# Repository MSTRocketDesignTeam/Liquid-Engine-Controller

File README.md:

<p align="center"><sup><em>*This repo is intended for educational purposes only*</em></sup></p>

# SRAD Engine Controller
A student researched and designed (SRAD) engine controller for the liquid bipropellant rocket. 

## About
This project is the first iteration of the flight controller for the Rocket Design Team's (RDT) liquid bipropellant rocket.
It aims to provide basic engine control functionality, such as opening and closing of the servo ball valves (SBV), as well as to set the hardware baseline for more advanced control functionality like throttling algorithms for flight efficiency. Additionally, the Liquid Engine Controller (LEC) aims to serve as the data acquisition computer for the propulsion system, in order to analyze the performance of the propulsion system. 

## Documentation
*placeholder*

## Development 
*placeholder* 

## File Structure
This repo contains three main sections, hardware, firmware, and software.

### Hardware:
The hardware directory will contain all of the files related to the design and assembly of the PCBs. This includes KiCad projects as well as BOMs. 

### Firmware:
The firmware directory will contain all of the code (C++) necessary to operate the above hardware. Once the boards have been designed and assembled this is where significant effort will be made.

### Software: 
The software directory will contain the code (Python) for the LEC's computer interface. This program will be responsible for configuring the LEC prior to launch as well as for displaying live propulsion system state data from the launch pad. 

Future developments may allow for preflight simulations (FEA / CFD of engine, estimated throttling curve, etc.).

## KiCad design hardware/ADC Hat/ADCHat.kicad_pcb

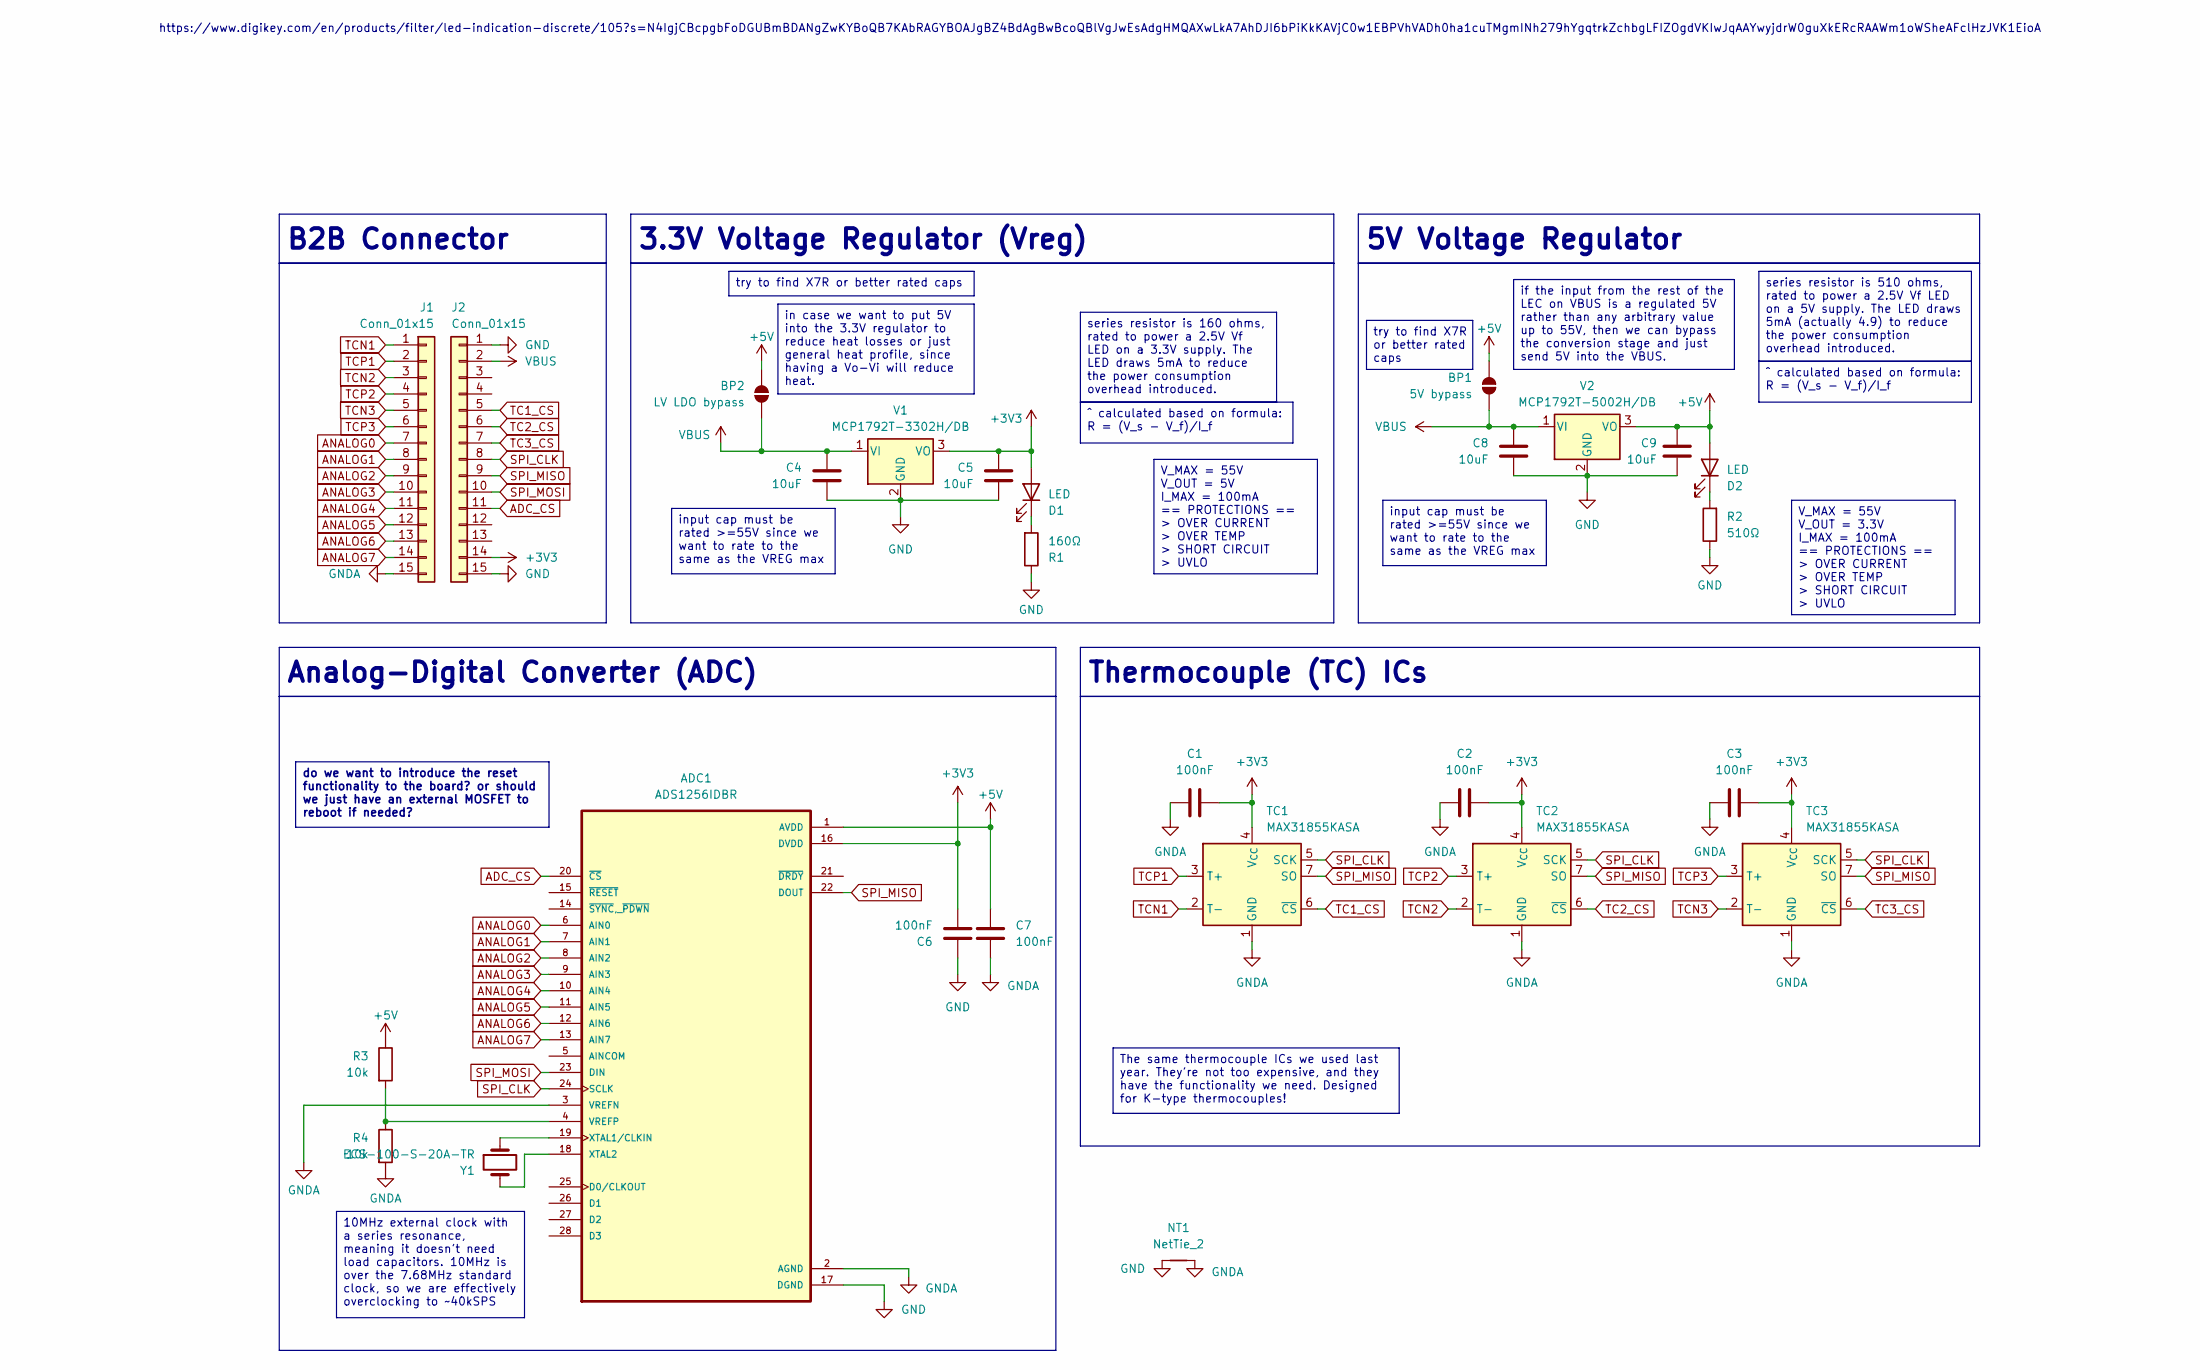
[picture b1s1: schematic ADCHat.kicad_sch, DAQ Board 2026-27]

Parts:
ADC1: ADS1256IDBR; SOP65P780X200-28N; DIGIKEY_ID ADS1256IDBR
BP1: 5V bypass; SolderJumper-2_P1.3mm_Open_RoundedPad1.0x1.5mm
BP2: LV LDO bypass; SolderJumper-2_P1.3mm_Open_RoundedPad1.0x1.5mm
C1, C2, C3: 100nF; C_0402_1005Metric; DIGIKEY_ID GRM155R71H104KE14D
C4, C8: 10uF; C_0805_2012Metric; DIGIKEY_ID GMC21X5R106K50NT
C5, C9: 10uF; C_0805_2012Metric; DIGIKEY_ID CL21A106KPFNNNG
C6, C7: 100nF; C_0805_2012Metric; DIGIKEY_ID CL21B104KBCNNNC
D1, D2: LED; LED_0603_1608Metric; DIGIKEY_ID KT EELP41.12-S2U1-25-2X4Y-5-R18
J1, J2: Conn_01x15; PinHeader_1x15_P2.54mm_Vertical
NT1: NetTie_2; NetTie-2_SMD_Pad0.5mm
R1: 160Ω; R_0603_1608Metric; DIGIKEY_ID RC0402FR-07160RL
R2: 510Ω; R_0603_1608Metric; DIGIKEY_ID RC0402FR-07510RL
R3, R4: 10k; R_0603_1608Metric; DIGIKEY_ID RNCF0402BTE10K0
TC1, TC2, TC3: MAX31855KASA; SOIC-8_3.9x4.9mm_P1.27mm; DIGIKEY_ID MAX31855KASA+T
V1: MCP1792T-3302H/DB; SOT-223-3_TabPin2; DIGIKEY_ID MCP1792T-3302H/DB
V2: MCP1792T-5002H/DB; SOT-223-3_TabPin2; DIGIKEY_ID MCP1792T-5002H/DB
Y1: ECS-100-S-20A-TR; XTAL_ECS-100-S-20A-TR; DIGIKEY_ID ECS-100-S-20A-TR

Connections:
+3V3: ADC1.16 (DVDD), C1.2, C2.2, C3.2, C5.1, C6.1, D1.2 (A), J2.14, TC1.4 (V_{CC}), TC2.4 (V_{CC}), TC3.4 (V_{CC}), V1.3 (VO)
+5V: ADC1.1 (AVDD), BP1.2 (B), BP2.2 (B), C7.2, C9.1, D2.2 (A), R3.1, V2.3 (VO)
ADC_CS: ADC1.20 (~CS), J2.11
ANALOG0: ADC1.6 (AIN0), J1.7
ANALOG1: ADC1.7 (AIN1), J1.8
ANALOG2: ADC1.8 (AIN2), J1.9
ANALOG3: ADC1.9 (AIN3), J1.10
ANALOG4: ADC1.10 (AIN4), J1.11
ANALOG5: ADC1.11 (AIN5), J1.12
ANALOG6: ADC1.12 (AIN6), J1.13
ANALOG7: ADC1.13 (AIN7), J1.14
GND: ADC1.17 (DGND), C4.2, C5.2, C6.2, C8.2, C9.2, J2.1, J2.15, NT1.1, R1.1, R2.1, V1.2 (GND), V2.2 (GND)
GNDA: ADC1.2 (AGND), ADC1.3 (VREFN), C1.1, C2.1, C3.1, C7.1, J1.15, NT1.2, R4.2, TC1.1 (GND), TC2.1 (GND), TC3.1 (GND)
unnamed: ADC1.4 (VREFP), R3.2, R4.1
unnamed: ADC1.19 (XTAL1/CLKIN), Y1.1
unnamed: ADC1.18 (XTAL2), Y1.2
unnamed: D1.1 (K), R1.2
unnamed: D2.1 (K), R2.2
SPI_CLK: ADC1.24 (SCLK), J2.8, TC1.5 (SCK), TC2.5 (SCK), TC3.5 (SCK)
SPI_MISO: ADC1.22 (DOUT), J2.9, TC1.7 (SO), TC2.7 (SO), TC3.7 (SO)
SPI_MOSI: ADC1.23 (DIN), J2.10
TC1_CS: J2.5, TC1.6 (~CS)
TC2_CS: J2.6, TC2.6 (~CS)
TC3_CS: J2.7, TC3.6 (~CS)
TCN1: J1.1, TC1.2 (T-)
TCN2: J1.3, TC2.2 (T-)
TCN3: J1.5, TC3.2 (T-)
TCP1: J1.2, TC1.3 (T+)
TCP2: J1.4, TC2.3 (T+)
TCP3: J1.6, TC3.3 (T+)
VBUS: BP1.1 (A), BP2.1 (A), C4.1, C8.1, J2.2, V1.1 (VI), V2.1 (VI)

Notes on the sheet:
https://www.digikey.com/en/products/filter/led-indication-discrete/105?s=N4IgjCBcpgbFoDGUBmBDANgZwKYBoQB7KAbRAGYBOAJgBZ4BdAgBwBcoQBlVgJwEsAdgHMQAXwLkA7AhDJI6bPiKkKAVjC0w1EBPVhVADh0ha1cuTMgmINh279hYgqtrkZchbgLFIZOgdVKIwJqAAYwyjdrW0guXkERcRAAWm1oWSheAFclHzJVK1EioA
10MHz external clock with a series resonance, meaning it doesn't need load capacitors. 10MHz is over the 7.68MHz standard clock, so we are effectively overclocking to ~40kSPS
in case we want to put 5V into the 3.3V regulator to reduce heat losses or just general heat profile, since having a Vo-Vi will reduce heat.
input cap must be rated >=55V since we want to rate to the same as the VREG max
5V Voltage Regulator
try to find X7R or better rated caps
V_MAX = 55V V_OUT = 5V I_MAX = 100mA == PROTECTIONS == > OVER CURRENT > OVER TEMP > SHORT CIRCUIT > UVLO
^ calculated based on formula: R = (V_s - V_f)/I_f
do we want to introduce the reset functionality to the board? or should we just have an external MOSFET to reboot if needed?
if the input from the rest of the LEC on VBUS is a regulated 5V rather than any arbitrary value up to 55V, then we can bypass the conversion stage and just send 5V into the VBUS.
Analog-Digital Converter (ADC)
The same thermocouple ICs we used last year. They're not too expensive, and they have the functionality we need. Designed for K-type thermocouples!
3.3V Voltage Regulator (Vreg)
V_MAX = 55V V_OUT = 3.3V I_MAX = 100mA == PROTECTIONS == > OVER CURRENT > OVER TEMP > SHORT CIRCUIT > UVLO
series resistor is 160 ohms, rated to power a 2.5V Vf LED on a 3.3V supply. The LED draws 5mA to reduce the power consumption overhead introduced.
series resistor is 510 ohms, rated to power a 2.5V Vf LED on a 5V supply. The LED draws 5mA (actually 4.9) to reduce the power consumption overhead introduced.
Thermocouple (TC) ICs
B2B Connector

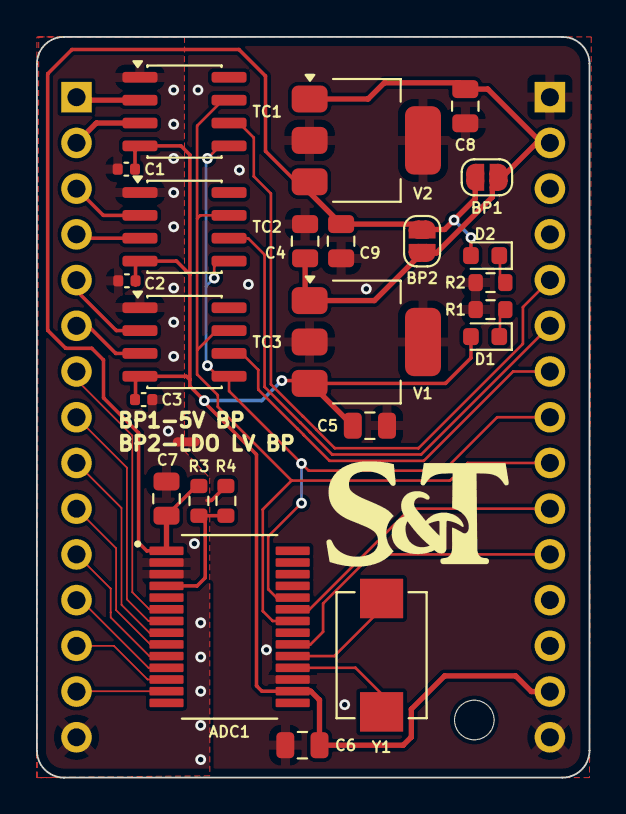
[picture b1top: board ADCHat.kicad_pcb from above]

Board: 2 copper layers, 30.7 x 41.1 mm, 27 parts (0 on the bottom side), 31 nets.

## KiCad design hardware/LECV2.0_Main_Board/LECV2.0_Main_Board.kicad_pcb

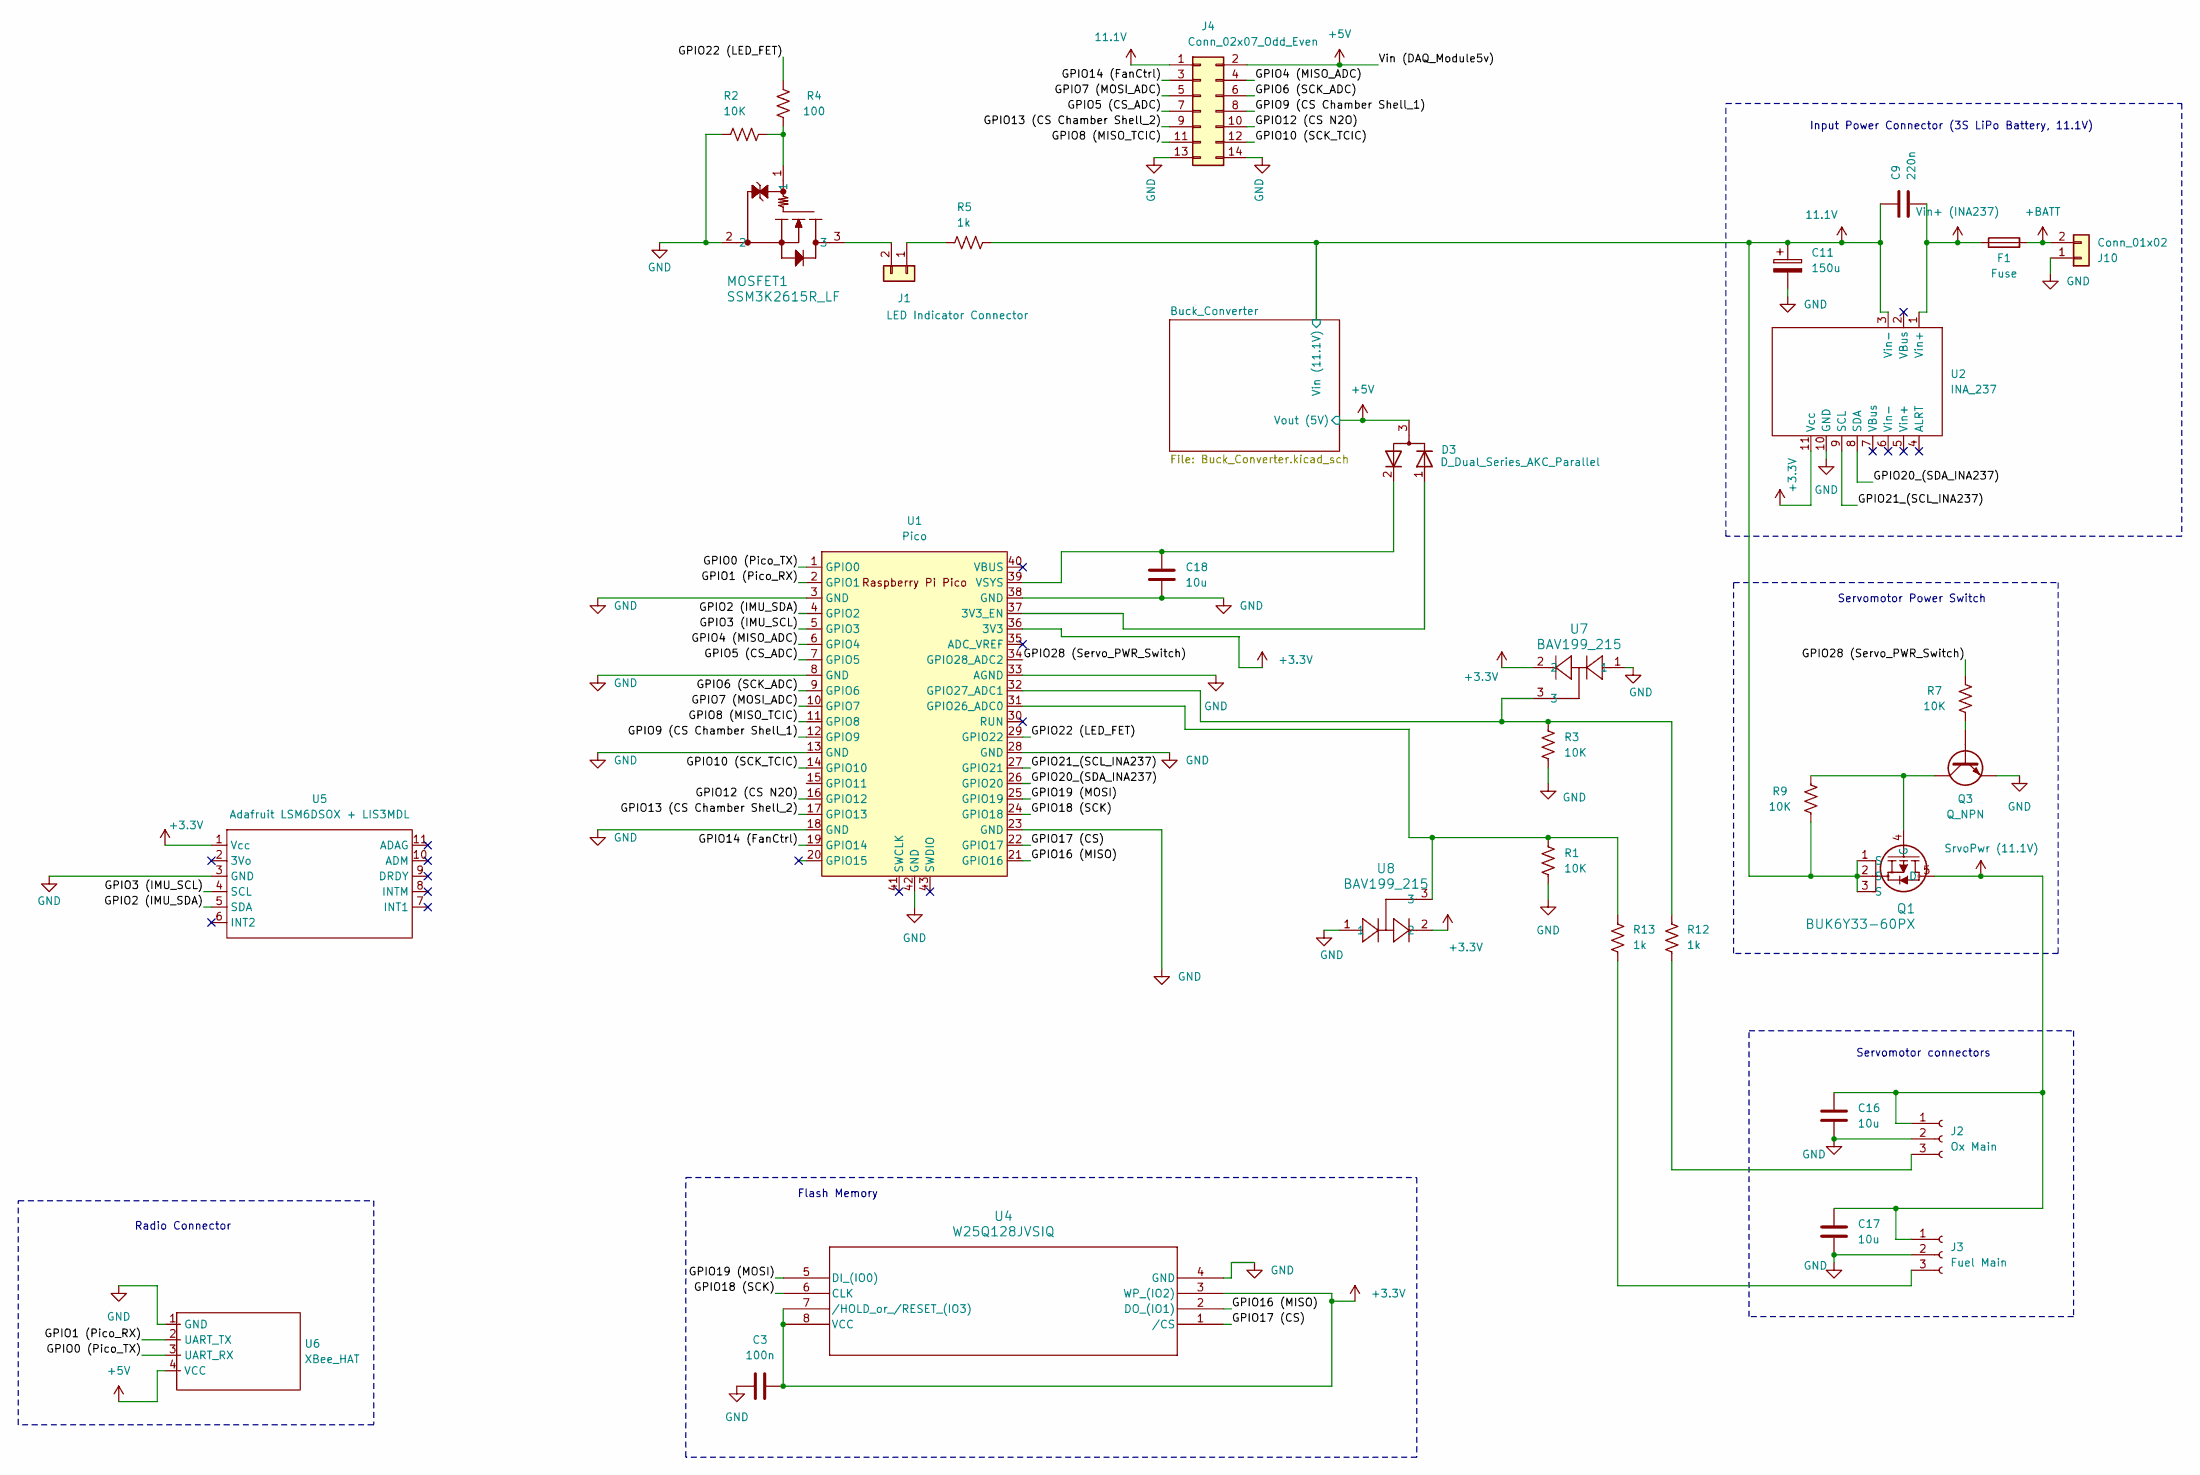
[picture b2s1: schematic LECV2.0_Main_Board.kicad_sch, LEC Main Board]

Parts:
C3: 100n; C_0603_1608Metric
C9: 220n; C_0805_2012Metric
C11: 150u; CAPPRD500W60D1000H1600
C16, C17, C18: 10u; C_1210_3225Metric
D3: D_Dual_Series_AKC_Parallel; SOT-23
F1: Fuse; Fuse_1206_3216Metric
J1: LED Indicator Connector; PinHeader_1x02_P2.54mm_Vertical
J2: Ox Main; TENSILITY_54-00440
J3: Fuel Main; TENSILITY_54-00440
J4: Conn_02x07_Odd_Even; PinHeader_2x07_P2.54mm_Vertical
J10: Conn_01x02; AMASS_XT30UPB-M_1x02_P5.0mm_Vertical
MOSFET1: SSM3K2615R_LF; SOT-23F_TOS
Q1: BUK6Y33-60PX; LFPAK_SOT669_NEX
Q3: Q_NPN; SOT-323_SC-70
R1, R2, R3, R7, R9: 10K; R_0603_1608Metric
R4: 100; R_0603_1608Metric
R5, R12, R13: 1k; R_0603_1608Metric
U1: Pico; RPi_Pico_SMD_TH
U2: INA_237; INA238_MODULE
U4: W25Q128JVSIQ; SOIC_128JVSIQ_WIN
U5: Adafruit LSM6DSOX + LIS3MDL; Adafruit_LSM6DSOX+LIS3MDL
U6: XBee_HAT; XBee-HAT
U7, U8: BAV199_215; SOT-23-3

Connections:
11.1V: C9.1, C11.1, J4.1, Q1.1 (S), Q1.2 (S), Q1.3 (S), R5.2, R9.1, U2.3 (Vin-); also elsewhere on the board
+3.3V: C3.2, U1.36 (3V3), U2.11 (Vcc), U4.3 (WP_(IO2)), U4.7 (/HOLD_or_/RESET_(IO3)), U4.8 (VCC), U5.1 (Vcc), U7.2, U8.2
+5V: D3.3 (common), J4.2, U6.4 (VCC); also elsewhere on the board
+BATT: F1.2, J10.2
/GPIO0 (Pico_TX): U1.1 (GPIO0), U6.3 (UART_RX)
/GPIO1 (Pico_RX): U1.2 (GPIO1), U6.2 (UART_TX)
/GPIO2 (IMU_SDA): U1.4 (GPIO2), U5.5 (SDA)
/GPIO3 (IMU_SCL): U1.5 (GPIO3), U5.4 (SCL)
/GPIO4 (MISO_ADC): J4.4, U1.6 (GPIO4)
/GPIO5 (CS_ADC): J4.7, U1.7 (GPIO5)
/GPIO6 (SCK_ADC): J4.6, U1.9 (GPIO6)
/GPIO7 (MOSI_ADC): J4.5, U1.10 (GPIO7)
/GPIO8 (MISO_TCIC): J4.11, U1.11 (GPIO8)
/GPIO9 (CS Chamber Shell_1): J4.8, U1.12 (GPIO9)
/GPIO10 (SCK_TCIC): J4.12, U1.14 (GPIO10)
/GPIO12 (CS N2O): J4.10, U1.16 (GPIO12)
/GPIO13 (CS Chamber Shell_2): J4.9, U1.17 (GPIO13)
/GPIO14 (FanCtrl): J4.3, U1.19 (GPIO14)
/GPIO16 (MISO): U1.21 (GPIO16), U4.2 (DO_(IO1))
/GPIO17 (CS): U1.22 (GPIO17), U4.1 (/CS)
/GPIO18 (SCK): U1.24 (GPIO18), U4.6 (CLK)
/GPIO19 (MOSI): U1.25 (GPIO19), U4.5 (DI_(IO0))
/GPIO20_(SDA_INA237): U1.26 (GPIO20), U2.8 (SDA)
/GPIO21_(SCL_INA237): U1.27 (GPIO21), U2.9 (SCL)
/GPIO22 (LED_FET): R4.1, U1.29 (GPIO22)
/GPIO28 (Servo_PWR_Switch): R7.2, U1.34 (GPIO28_ADC2)
GND: C3.1, C11.2, C16.2, C17.2, C18.2, J2.2, J3.2, J4.13, J4.14, J10.1, MOSFET1.2, Q3.2 (E), R1.2, R2.2, R3.2, U1.3 (GND), U1.8 (GND), U1.13 (GND), U1.18 (GND), U1.23 (GND), U1.28 (GND), U1.33 (AGND), U1.38 (GND), U1.42 (GND), U2.10 (GND), U4.4 (GND), U5.3 (GND), U6.1 (GND), U7.1, U8.1; also elsewhere on the board
unnamed: D3.1 (A), U1.37 (3V3_EN)
unnamed: C18.1, D3.2 (K), U1.39 (VSYS)
unnamed: J1.1, R5.1
unnamed: J1.2, MOSFET1.3
unnamed: J2.3, R12.2
unnamed: J3.3, R13.2
unnamed: MOSFET1.1, R2.1, R4.2
unnamed: Q1.4 (G), Q3.3 (C), R9.2
unnamed: Q3.1 (B), R7.1
unnamed: R1.1, R13.1, U1.31 (GPIO26_ADC0), U8.3
unnamed: R3.1, R12.1, U1.32 (GPIO27_ADC1), U7.3
SrvoPwr (11.1V): C16.1, C17.1, J2.1, J3.1, Q1.5 (D)
Vin+ (INA237): C9.2, F1.1, U2.1 (Vin+)

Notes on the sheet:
Flash Memory
Radio Connector
Servomotor Power Switch
Input Power Connector (3S LiPo Battery, 11.1V)
Servomotor connectors

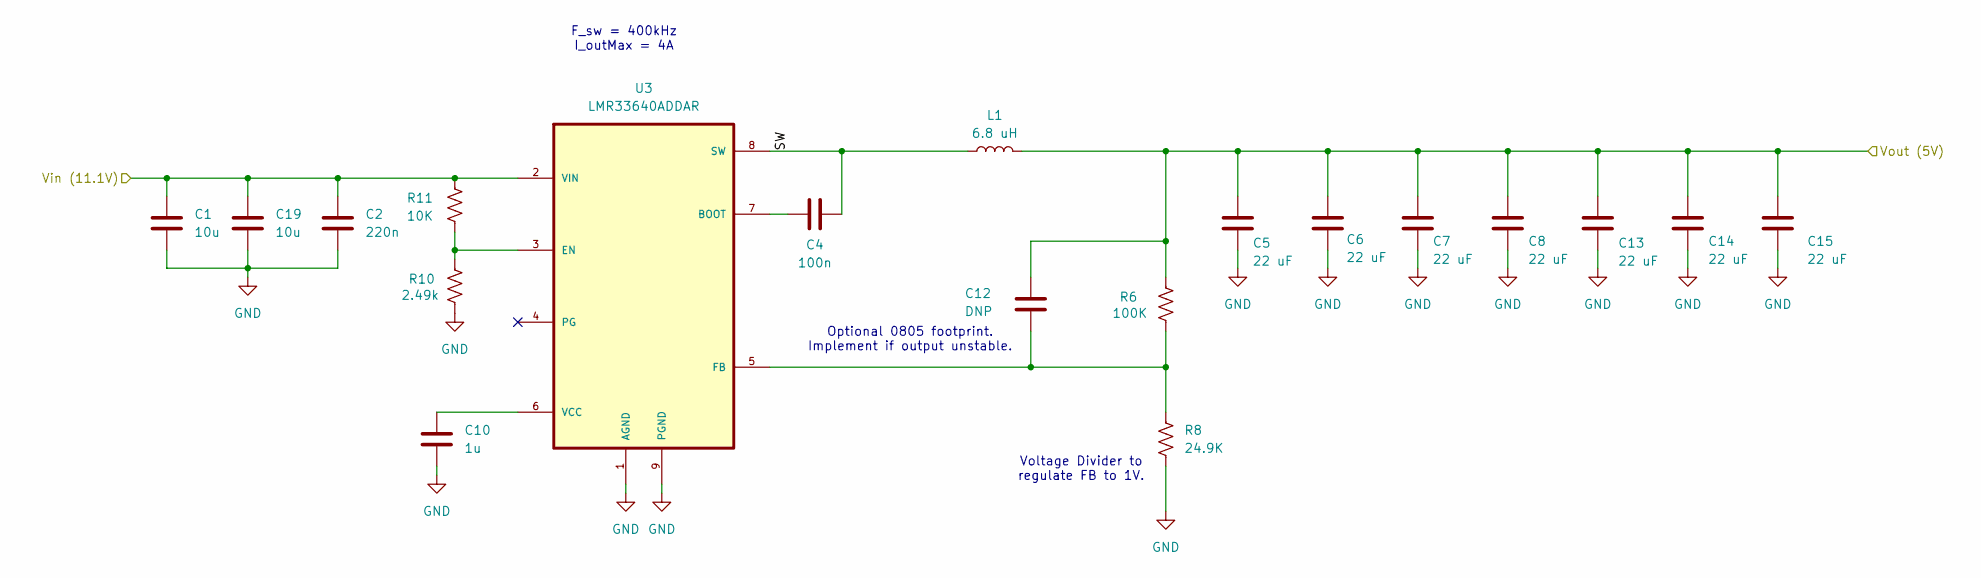
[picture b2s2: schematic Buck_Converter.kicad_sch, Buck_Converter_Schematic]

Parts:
C1, C19: 10u; C_1210_3225Metric
C2: 220n; C_0805_2012Metric
C4: 100n; C_0603_1608Metric
C5, C6, C7, C8, C13, C14, C15: 22 uF; C_0805_2012Metric
C10: 1u; C_0805_2012Metric
C12: DNP; C_0805_2012Metric
L1: 6.8 uH; IND_CSBX0650-6R8M
R6: 100K; R_0603_1608Metric
R8: 24.9K; R_0603_1608Metric
R10: 2.49k; R_0603_1608Metric
R11: 10K; R_0603_1608Metric
U3: LMR33640ADDAR; Texas_HSOP-8-1EP_3.9x4.9mm_P1.27mm_ThermalVias

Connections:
11.1V: C1.1, C2.1, C19.1, R11.1, U3.2 (VIN); also elsewhere on the board
+5V: C5.1, C6.1, C7.1, C8.1, C12.2, C13.1, C14.1, C15.1, L1.2, R6.2; also elsewhere on the board
/Buck_Converter/SW: C4.2, L1.1, U3.8 (SW)
GND: C1.2, C2.2, C5.2, C6.2, C7.2, C8.2, C10.2, C13.2, C14.2, C15.2, C19.2, R8.2, R10.1, U3.1 (AGND), U3.9 (PGND); also elsewhere on the board
unnamed: C4.1, U3.7 (BOOT)
unnamed: R10.2, R11.2, U3.3 (EN)
unnamed: C12.1, R6.1, R8.1, U3.5 (FB)
unnamed: C10.1, U3.6 (VCC)

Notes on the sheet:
Optional 0805 footprint. Implement if output unstable.
Voltage Divider to regulate FB to 1V.
F_sw = 400kHz I_outMax = 4A

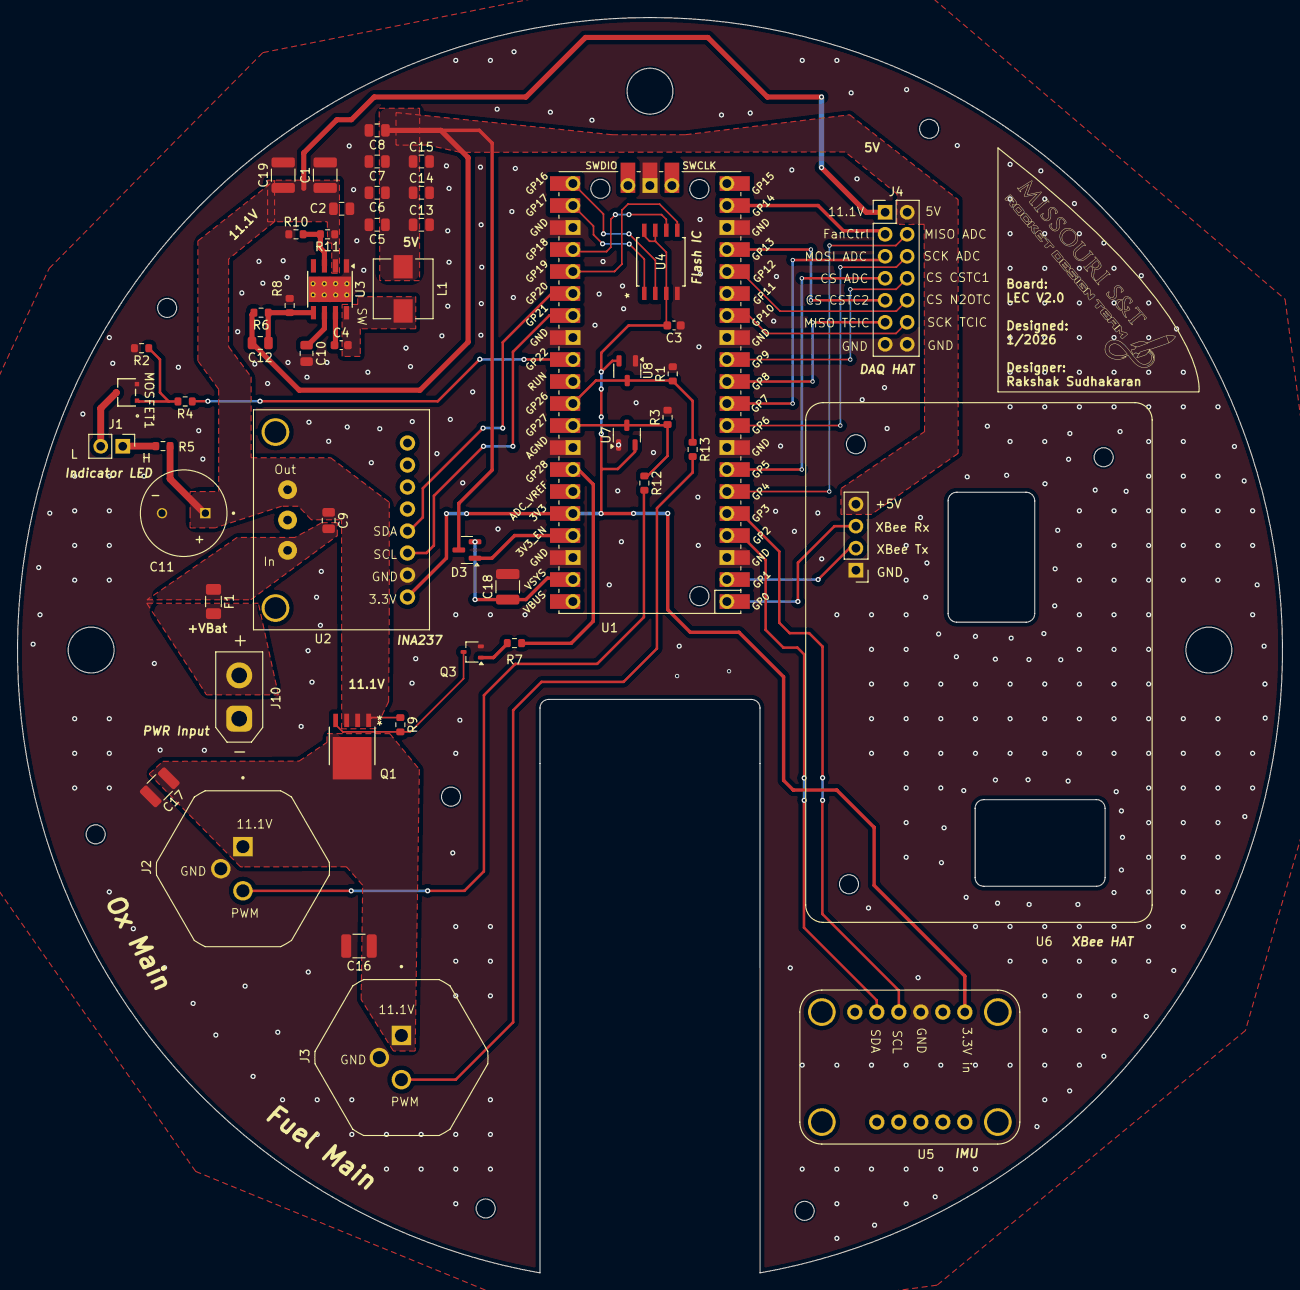
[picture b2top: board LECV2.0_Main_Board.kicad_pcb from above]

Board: 2 copper layers, 146.0 x 144.9 mm, 51 parts (0 on the bottom side), 45 nets.

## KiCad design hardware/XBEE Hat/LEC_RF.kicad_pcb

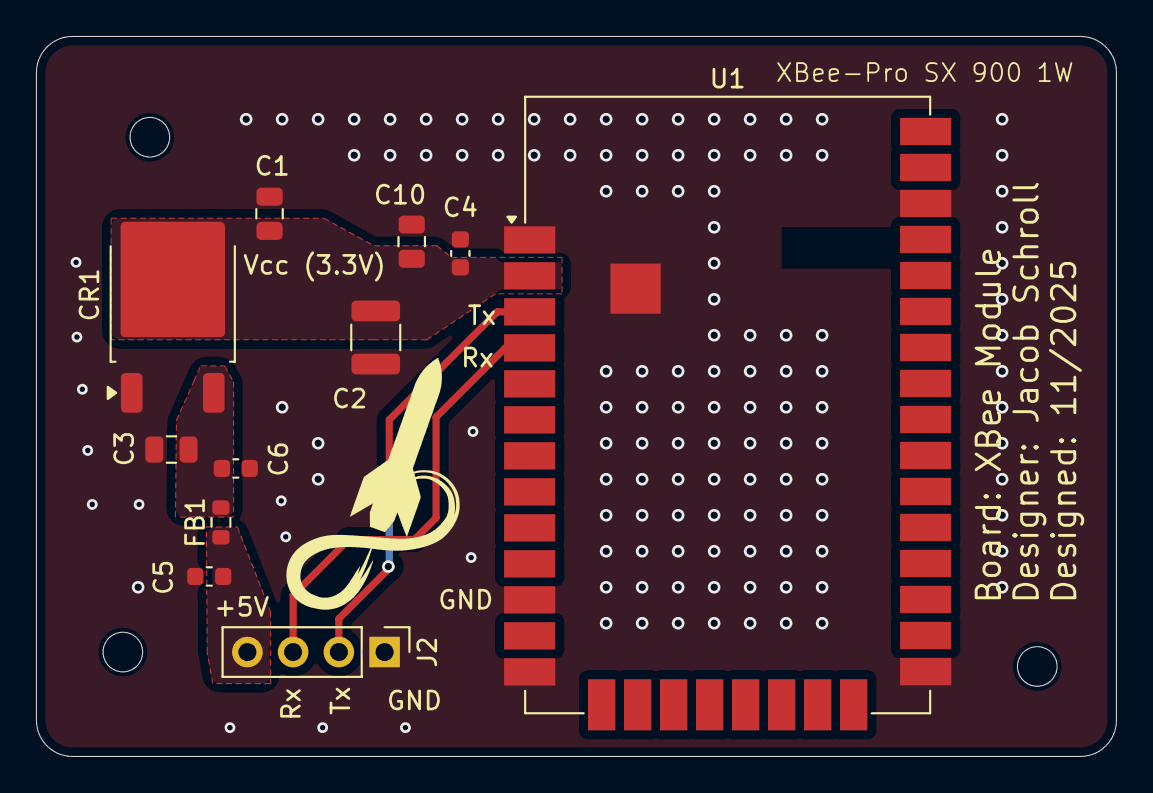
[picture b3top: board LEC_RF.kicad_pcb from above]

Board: 2 copper layers, 60.0 x 40.0 mm, 11 parts (0 on the bottom side), 6 nets.

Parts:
C1: 22uF; C_0805_2012Metric
C2: 10u; C_1210_3225Metric
C3: 10uF; C_0805_2012Metric
C4, C5, C6: 100n; C_0603_1608Metric
C10: 1u; C_0805_2012Metric
CR1: LD1086DT33TR; TO-252-2
FB1: FerriteBead; R_0603_1608Metric
J2: Conn_01x04; PinHeader_1x04_P2.54mm_Vertical
U1: XBP9X-DMUS-001; XBEE_GND_PAD

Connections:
+5V: C5.2, FB1.1, J2.4
+5V_Filt: C3.1, C6.2, CR1.3 (INPUT), FB1.2
/UART_RX: J2.3, U1.4 (DIO14/UART_RX/~CONFIG)
/UART_TX: J2.2, U1.3 (DIO13/UART_TX)
GND: C1.2, C2.2, C3.2, C4.1, C5.1, C6.1, C10.2, CR1.1 (ADJ/GND), J2.1, U1.1 (GND), U1.11 (GND), U1.13 (GND), U1.22 (GND), U1.35 (GND), U1.38 (GND)
VCC: C1.1, C2.1, C4.2, C10.1, CR1.2 (OUTPUT), U1.2 (VCC)

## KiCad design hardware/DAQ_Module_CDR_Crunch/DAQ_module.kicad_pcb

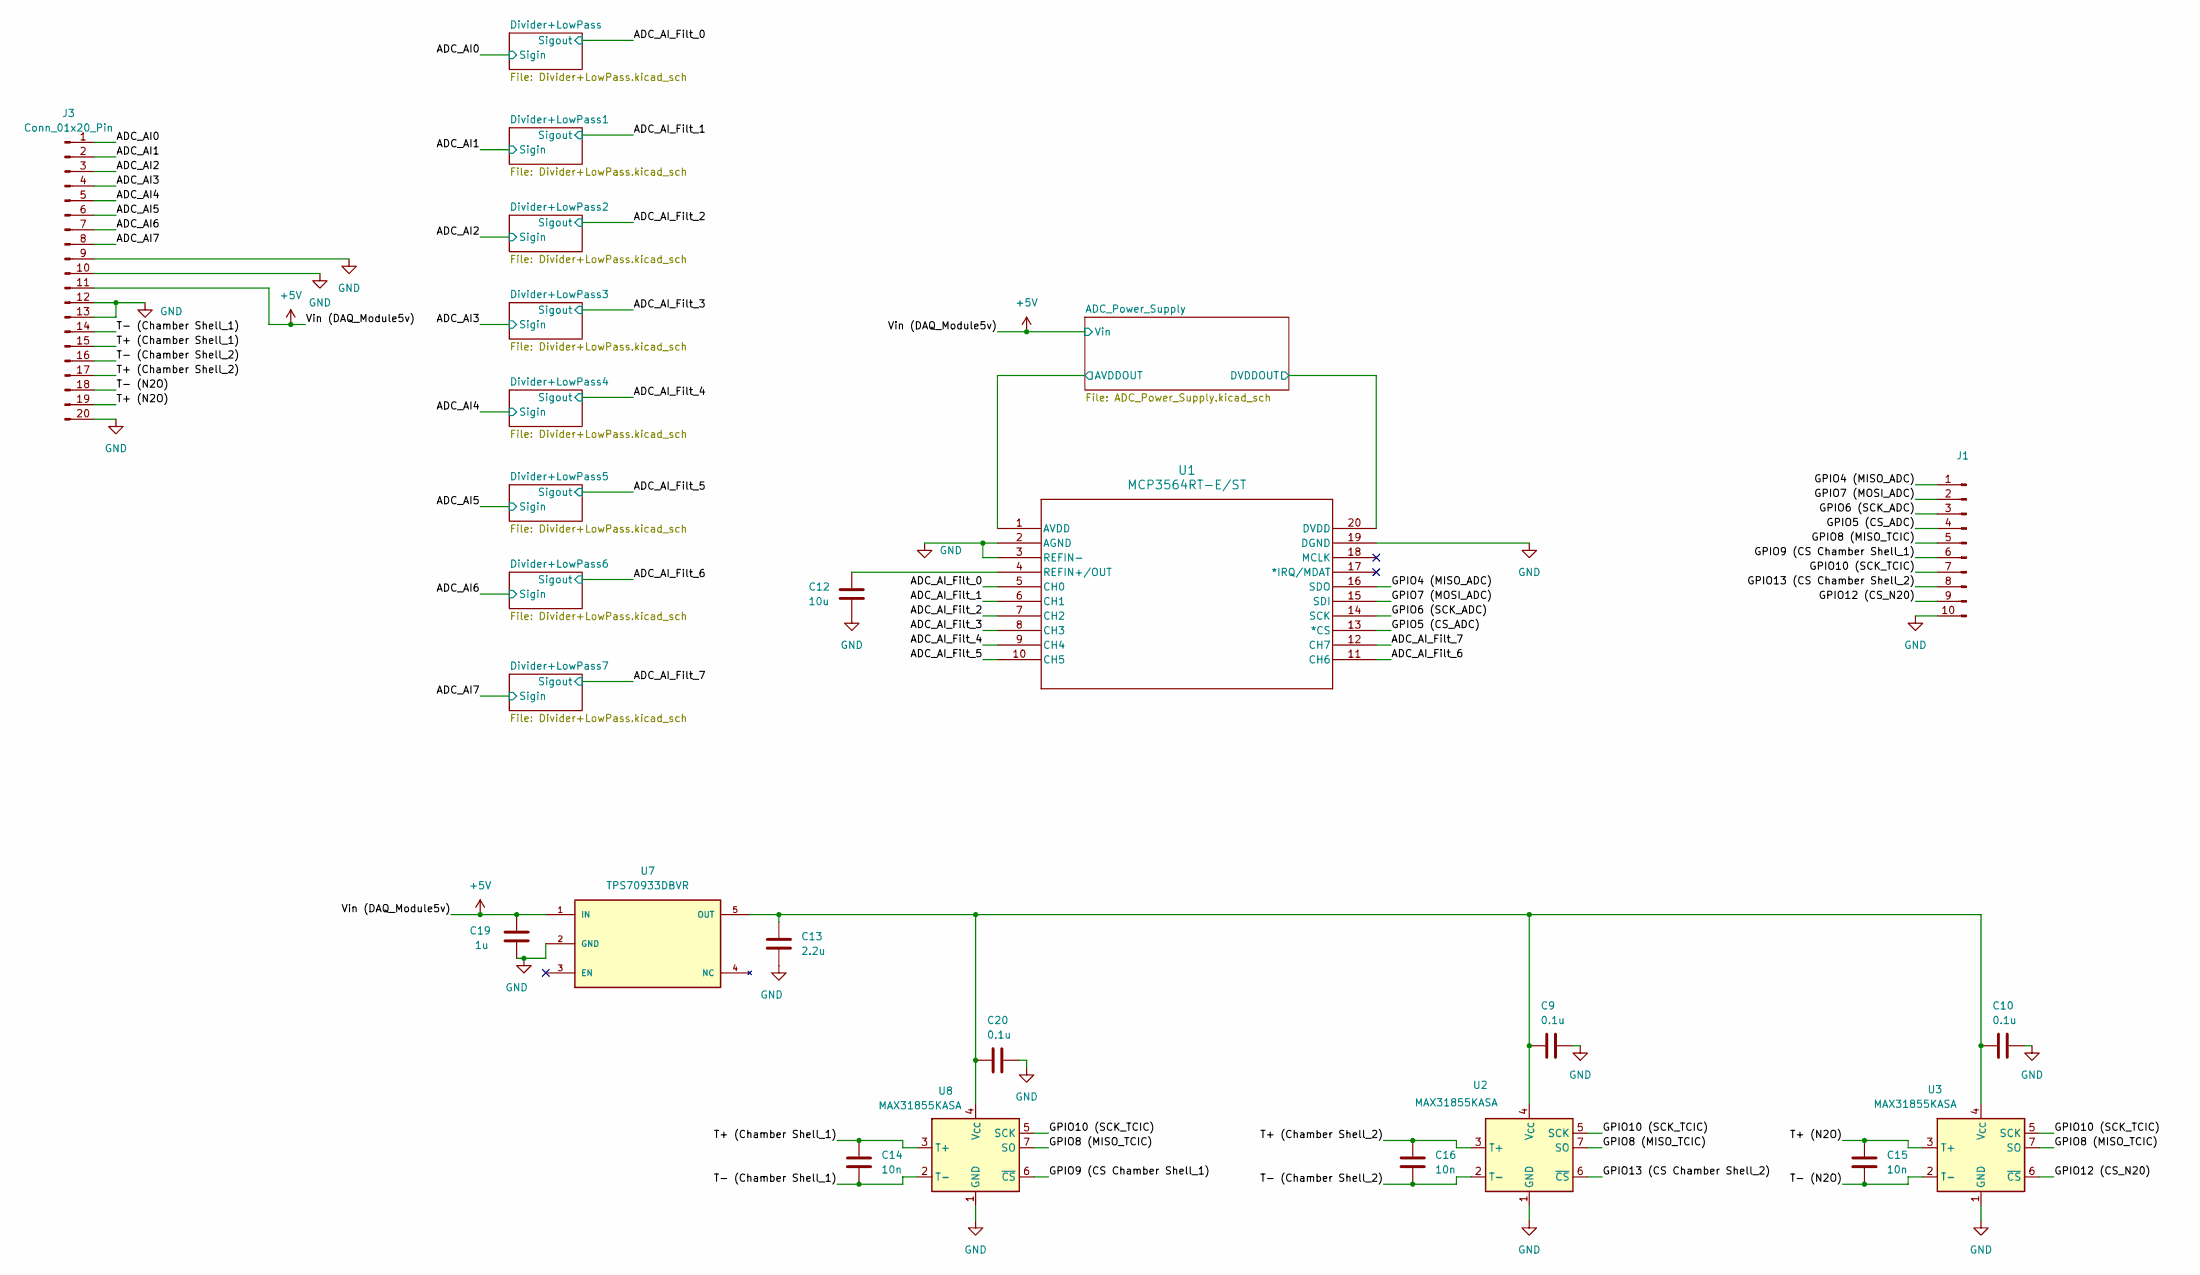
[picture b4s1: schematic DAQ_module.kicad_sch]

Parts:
C9, C10, C20: 0.1u; C_0603_1608Metric
C12: 10u; C_0805_2012Metric
C13: 2.2u; C_1206_3216Metric
C14, C15, C16: 10n; C_0603_1608Metric
C19: 1u; C_0805_2012Metric
J1: Conn_01x10_Pin; PinHeader_1x10_P2.54mm_Vertical
J3: Conn_01x20_Pin; PinHeader_1x20_P2.54mm_Vertical
U1: MCP3564RT-E/ST; TSSOP20_ST_MCH
U2, U3, U8: MAX31855KASA; SOIC-8_3.9x4.9mm_P1.27mm
U7: TPS70933DBVR; DBV5_TEX; PARTREV H

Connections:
+5V: C19.2, J3.11, U7.1 (IN); also elsewhere on the board
/ADC_AI0: J3.1; also elsewhere on the board
/ADC_AI1: J3.2; also elsewhere on the board
/ADC_AI2: J3.3; also elsewhere on the board
/ADC_AI3: J3.4; also elsewhere on the board
/ADC_AI4: J3.5; also elsewhere on the board
/ADC_AI5: J3.6; also elsewhere on the board
/ADC_AI6: J3.7; also elsewhere on the board
/ADC_AI7: J3.8; also elsewhere on the board
/ADC_AI_Filt_0: U1.5 (CH0); also elsewhere on the board
/ADC_AI_Filt_1: U1.6 (CH1); also elsewhere on the board
/ADC_AI_Filt_2: U1.7 (CH2); also elsewhere on the board
/ADC_AI_Filt_3: U1.8 (CH3); also elsewhere on the board
/ADC_AI_Filt_4: U1.9 (CH4); also elsewhere on the board
/ADC_AI_Filt_5: U1.10 (CH5); also elsewhere on the board
/ADC_AI_Filt_6: U1.11 (CH6); also elsewhere on the board
/ADC_AI_Filt_7: U1.12 (CH7); also elsewhere on the board
/ADC_Power_Supply/AVDDOUT: U1.1 (AVDD); also elsewhere on the board
/ADC_Power_Supply/DVDDOUT: U1.20 (DVDD); also elsewhere on the board
/GPIO4 (MISO_ADC): J1.1, U1.16 (SDO)
/GPIO5 (CS_ADC): J1.4, U1.13 (*CS)
/GPIO6 (SCK_ADC): J1.3, U1.14 (SCK)
/GPIO7 (MOSI_ADC): J1.2, U1.15 (SDI)
/GPIO8 (MISO_TCIC): J1.5, U2.7 (SO), U3.7 (SO), U8.7 (SO)
/GPIO9 (CS Chamber Shell_1): J1.6, U8.6 (~CS)
/GPIO10 (SCK_TCIC): J1.7, U2.5 (SCK), U3.5 (SCK), U8.5 (SCK)
/GPIO12 (CS_N20): J1.9, U3.6 (~CS)
/GPIO13 (CS Chamber Shell_2): J1.8, U2.6 (~CS)
/T+ (Chamber Shell_1): C14.1, J3.15, U8.3 (T+)
/T+ (Chamber Shell_2): C16.1, J3.17, U2.3 (T+)
/T+ (N2O): C15.1, J3.19, U3.3 (T+)
/T- (Chamber Shell_1): C14.2, J3.14, U8.2 (T-)
/T- (Chamber Shell_2): C16.2, J3.16, U2.2 (T-)
/T- (N2O): C15.2, J3.18, U3.2 (T-)
GND: C9.2, C10.2, C12.1, C13.2, C19.1, C20.2, J1.10, J3.9, J3.10, J3.12, J3.13, J3.20, U1.2 (AGND), U1.3 (REFIN-), U1.19 (DGND), U2.1 (GND), U3.1 (GND), U7.2 (GND), U8.1 (GND); also elsewhere on the board
unnamed: C12.2, U1.4 (REFIN+/OUT)
unnamed: C9.1, C10.1, C13.1, C20.1, U2.4 (V_{CC}), U3.4 (V_{CC}), U7.5 (OUT), U8.4 (V_{CC})

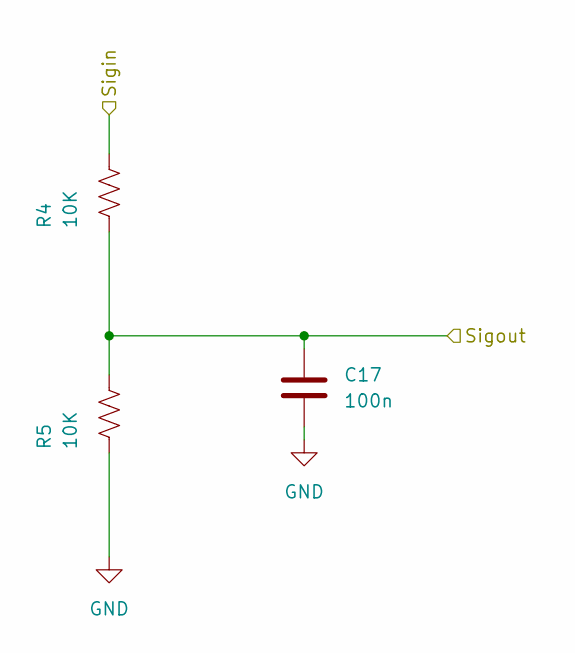
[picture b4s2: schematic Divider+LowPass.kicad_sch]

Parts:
C17: 100n; C_0603_1608Metric
R4, R5: 10K; R_0603_1608Metric

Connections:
/ADC_AI1: R4.1; also elsewhere on the board
/ADC_AI_Filt_1: C17.2, R4.2, R5.1; also elsewhere on the board
GND: C17.1, R5.2; also elsewhere on the board

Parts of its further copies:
C11, C21, C22, C23, C24, C25, C26: 100n; C_0603_1608Metric
R2, R3, R6, R7, R8, R9, R10, R11, R12, R13, R14, R15, R16, R17: 10K; R_0603_1608Metric

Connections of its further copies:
/ADC_AI0: R3.1; also elsewhere on the board
/ADC_AI2: R6.1; also elsewhere on the board
/ADC_AI3: R8.1; also elsewhere on the board
/ADC_AI4: R10.1; also elsewhere on the board
/ADC_AI5: R12.1; also elsewhere on the board
/ADC_AI6: R14.1; also elsewhere on the board
/ADC_AI7: R16.1; also elsewhere on the board
/ADC_AI_Filt_0: C11.2, R2.1, R3.2; also elsewhere on the board
/ADC_AI_Filt_2: C21.2, R6.2, R7.1; also elsewhere on the board
/ADC_AI_Filt_3: C22.2, R8.2, R9.1; also elsewhere on the board
/ADC_AI_Filt_4: C23.2, R10.2, R11.1; also elsewhere on the board
/ADC_AI_Filt_5: C24.2, R12.2, R13.1; also elsewhere on the board
/ADC_AI_Filt_6: C25.2, R14.2, R15.1; also elsewhere on the board
/ADC_AI_Filt_7: C26.2, R16.2, R17.1; also elsewhere on the board
GND: C11.1, C21.1, C22.1, C23.1, C24.1, C25.1, C26.1, R2.2, R7.2, R9.2, R11.2, R13.2, R15.2, R17.2; also elsewhere on the board

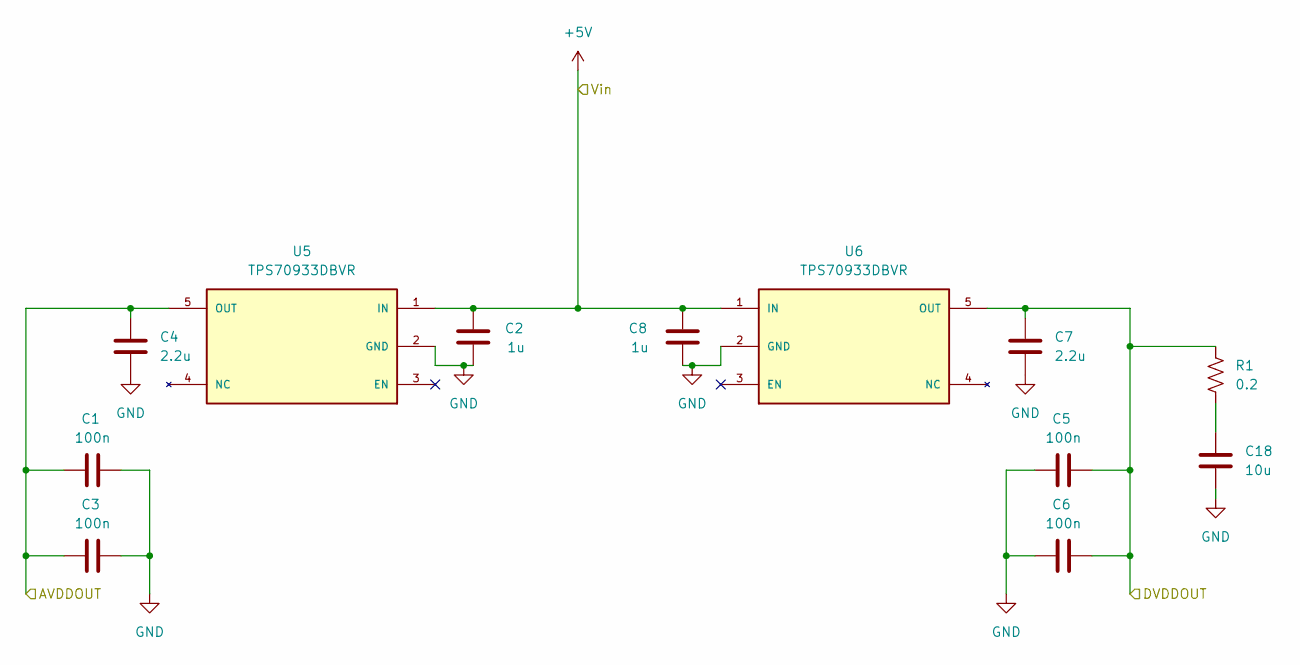
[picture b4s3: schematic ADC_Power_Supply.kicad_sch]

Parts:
C1, C3, C5, C6: 100n; C_0603_1608Metric
C2, C8: 1u; C_0805_2012Metric
C4, C7: 2.2u; C_1206_3216Metric
C18: 10u; C_1210_3225Metric
R1: 0.2; R_0603_1608Metric
U5, U6: TPS70933DBVR; DBV5_TEX; PARTREV H

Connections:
+5V: C2.2, C8.1, U5.1 (IN), U6.1 (IN); also elsewhere on the board
/ADC_Power_Supply/AVDDOUT: C1.2, C3.2, C4.1, U5.5 (OUT); also elsewhere on the board
/ADC_Power_Supply/DVDDOUT: C5.1, C6.1, C7.1, R1.1, U6.5 (OUT); also elsewhere on the board
GND: C1.1, C2.1, C3.1, C4.2, C5.2, C6.2, C7.2, C8.2, C18.2, U5.2 (GND), U6.2 (GND); also elsewhere on the board
unnamed: C18.1, R1.2
